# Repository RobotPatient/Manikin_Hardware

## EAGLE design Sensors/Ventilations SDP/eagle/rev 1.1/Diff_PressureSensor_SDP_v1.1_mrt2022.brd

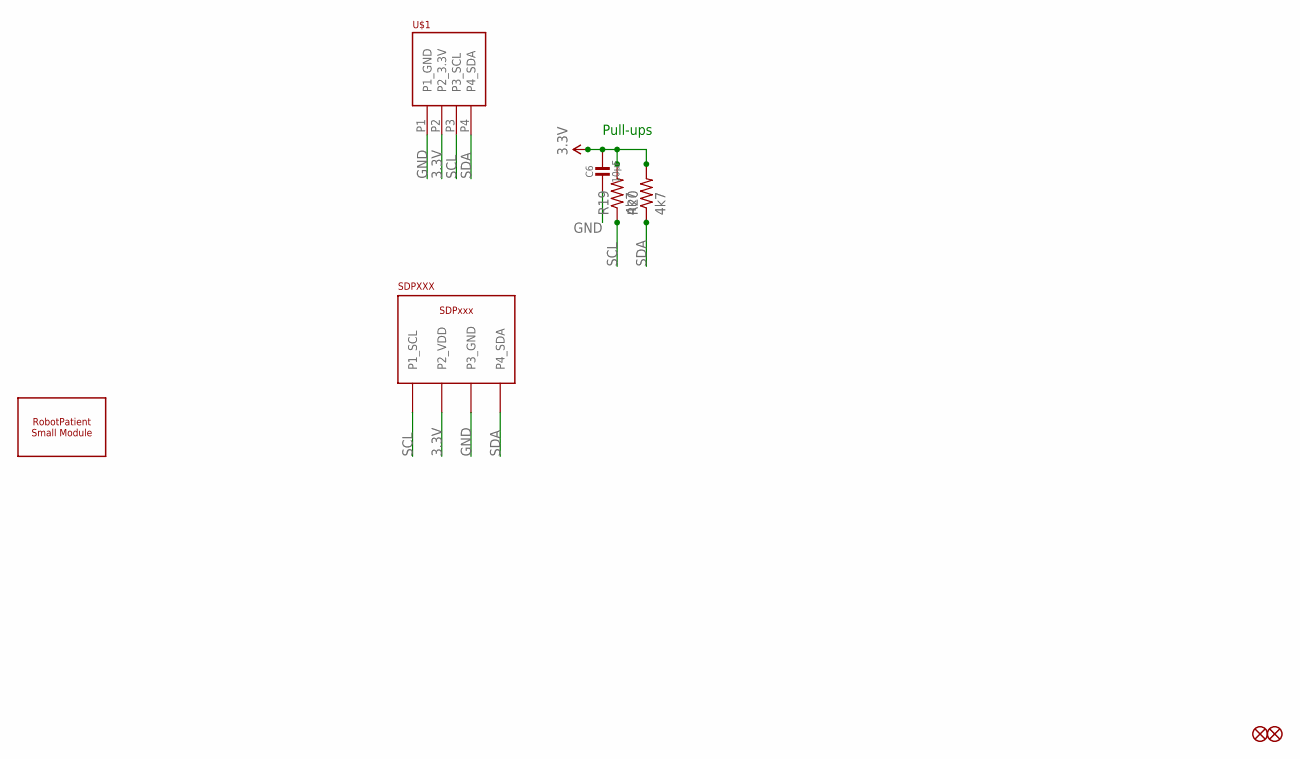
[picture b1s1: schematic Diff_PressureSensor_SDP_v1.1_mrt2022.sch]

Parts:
C6: 10µF; 0805-NO
FID1, FID2: FIDUCIAL""; FIDUCIAL_1MM
R19, R20: 4k7; 0603-RES
SDP810: SDPXXX
U$1: PHOENIX_PTSM_M4_THANGLE; PTSM_M4_TH
U$2: ROBOTPATIENT_SMALL_MODULEBOARD; RP_SMALL_SENSOR_OUTLINE

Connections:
3.3V: C6.1, R19.2, R20.2, SDP810.P3_VCC (P2_VDD), U$1.P2 (P2_3.3V)
GND: C6.2, SDP810.P2_GND (P3_GND), U$1.P1 (P1_GND)
SCL: R19.1, SDP810.P4_CLK (P1_SCL), U$1.P3 (P3_SCL)
SDA: R20.1, SDP810.P1_SDA (P4_SDA), U$1.P4 (P4_SDA)

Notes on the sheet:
Pull-ups

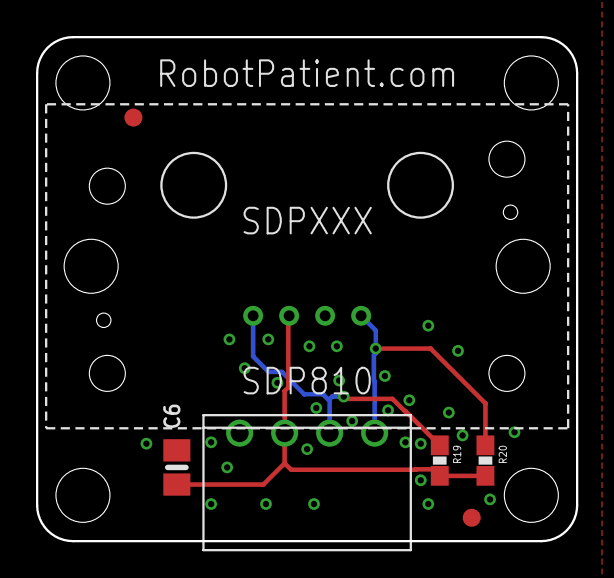
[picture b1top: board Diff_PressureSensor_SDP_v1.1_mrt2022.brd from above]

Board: 2 copper layers, 30.0 x 28.0 mm, 8 parts (0 on the bottom side), 4 nets.

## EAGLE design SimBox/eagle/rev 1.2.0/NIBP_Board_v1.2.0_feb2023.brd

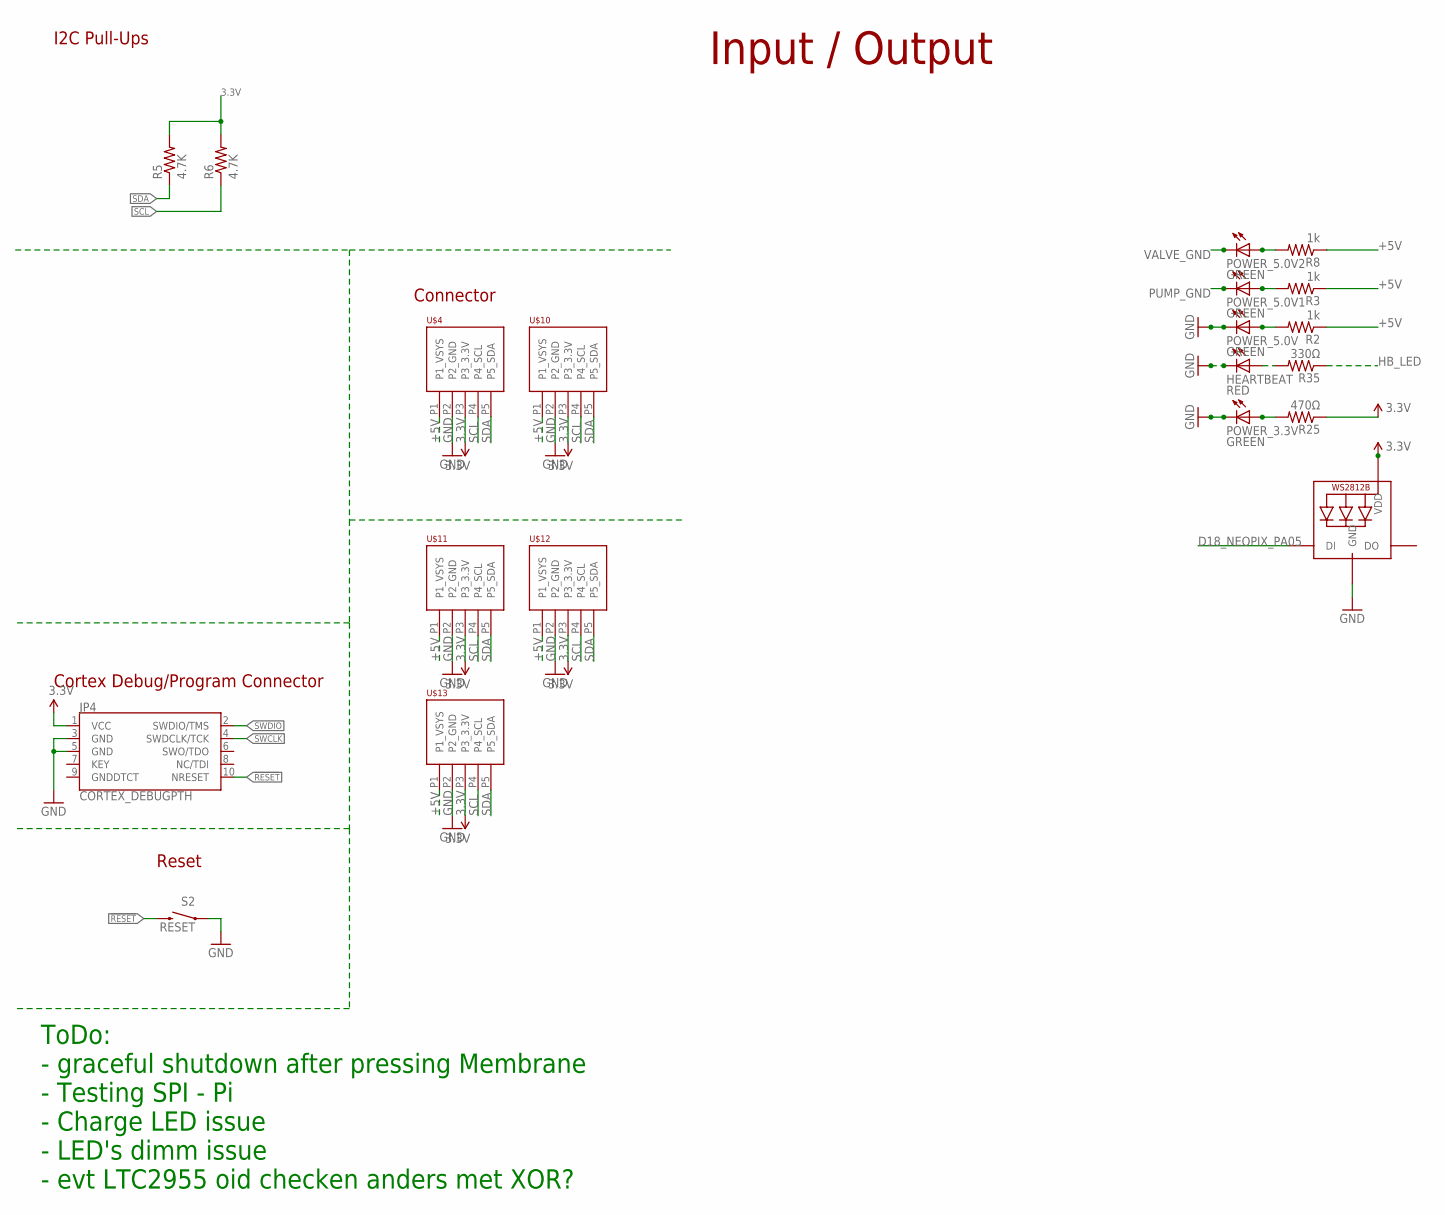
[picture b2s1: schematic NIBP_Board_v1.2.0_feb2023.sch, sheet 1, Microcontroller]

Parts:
HEARTBEAT: RED; LED-0603
JP4: CORTEX_DEBUGPTH; 2X5-PTH-1.27MM
LED1: WS2812B3535; LED3535
POWER_3.3V, POWER_5.0V, POWER_5.0V1, POWER_5.0V2: GREEN; LED-0603
R2, R3, R8: 1k; 0603-RES
R5, R6: 4.7K; 0603-RES@1
R25: 470Ω; 0603-RES
R35: 330Ω; 0603-RES
S2: RESET; TACTILE_SWITCH_SMD_4.6X2.8MM
U$4, U$10, U$11, U$12, U$13: PHOENIX_PTSM_M5_TH; PTSM_M5_THRHOLE

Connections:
3.3V: JP4.1 (VCC), LED1.2 (VDD), R5.2, R6.2, R25.1, U$4.P3 (P3_3.3V), U$10.P3 (P3_3.3V), U$11.P3 (P3_3.3V), U$12.P3 (P3_3.3V), U$13.P3 (P3_3.3V); also elsewhere on the board
!RESET: JP4.10 (NRESET), S2.3 (2), S2.4 (2); also elsewhere on the board
+5V: R2.1, R3.1, R8.1, U$4.P1 (P1_VSYS), U$10.P1 (P1_VSYS), U$11.P1 (P1_VSYS), U$12.P1 (P1_VSYS), U$13.P1 (P1_VSYS); also elsewhere on the board
D18_NEOPIX_PA05: LED1.1 (DI); also elsewhere on the board
GND: HEARTBEAT.C, JP4.3 (GND), JP4.5 (GND), LED1.4 (GND), POWER_3.3V.C, POWER_5.0V.C, S2.1, S2.2 (1), U$4.P2 (P2_GND), U$10.P2 (P2_GND), U$11.P2 (P2_GND), U$12.P2 (P2_GND), U$13.P2 (P2_GND); also elsewhere on the board
HB_LED: R35.1; also elsewhere on the board
unnamed: POWER_5.0V.A, R2.2
unnamed: POWER_5.0V1.A, R3.2
unnamed: POWER_5.0V2.A, R8.2
unnamed: POWER_3.3V.A, R25.2
unnamed: HEARTBEAT.A, R35.2
PUMP_GND: POWER_5.0V1.C; also elsewhere on the board
SCL: R6.1, U$4.P4 (P4_SCL), U$10.P4 (P4_SCL), U$11.P4 (P4_SCL), U$12.P4 (P4_SCL), U$13.P4 (P4_SCL); also elsewhere on the board
SDA: R5.1, U$4.P5 (P5_SDA), U$10.P5 (P5_SDA), U$11.P5 (P5_SDA), U$12.P5 (P5_SDA), U$13.P5 (P5_SDA); also elsewhere on the board
SWCLK: JP4.4 (SWDCLK/TCK); also elsewhere on the board
SWDIO: JP4.2 (SWDIO/TMS); also elsewhere on the board
VALVE_GND: POWER_5.0V2.C; also elsewhere on the board

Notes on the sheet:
Cortex Debug/Program Connector
I2C Pull-Ups
Input / Output
Connector
Reset
ToDo: - graceful shutdown after pressing Membrane - Testing SPI - Pi - Charge LED issue - LED's dimm issue - evt LTC2955 oid checken anders met XOR?

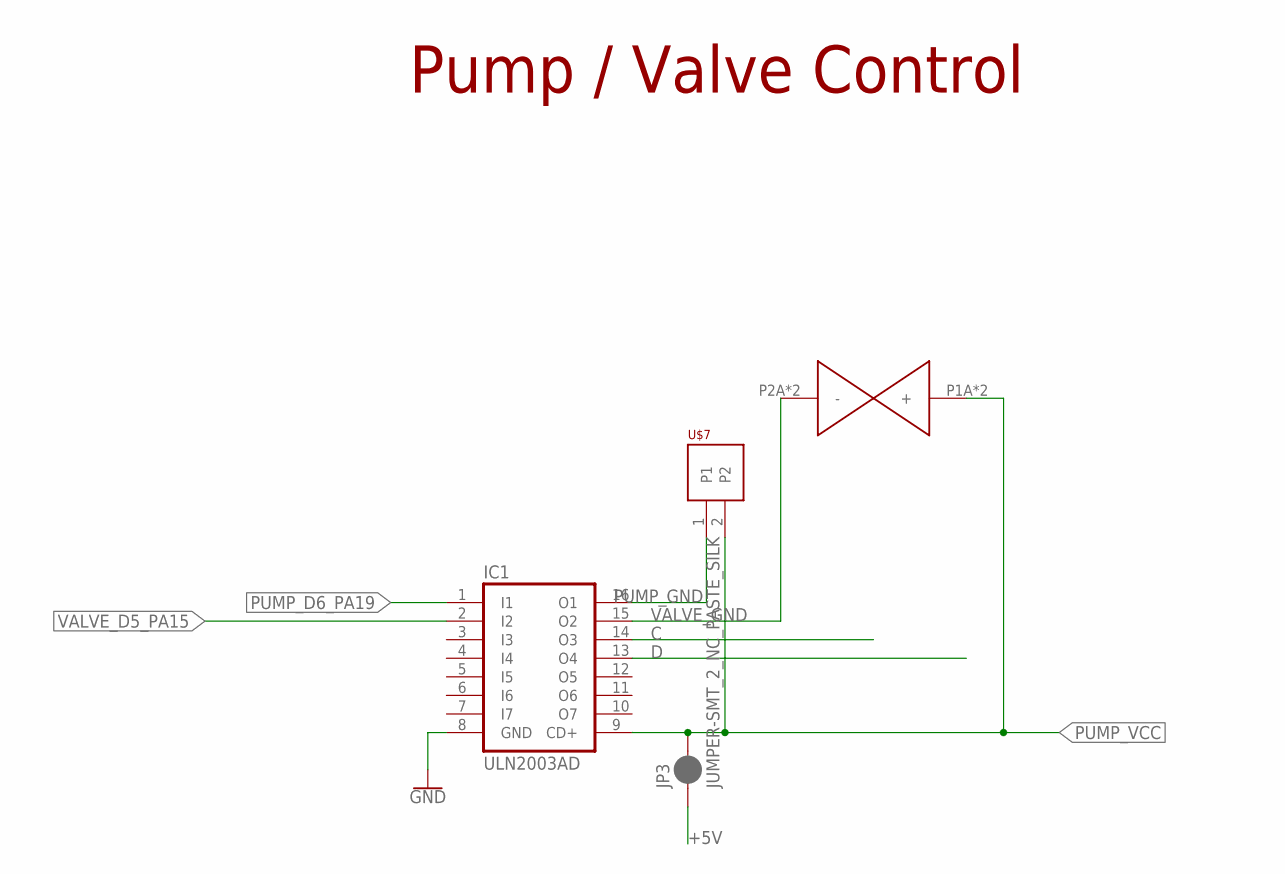
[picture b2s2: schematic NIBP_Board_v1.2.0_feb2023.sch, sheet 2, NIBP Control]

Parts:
IC1: ULN2003AD; SO16
JP3: JUMPER-SMT_2_NC_PASTE_SILK; SMT-JUMPER_2_NC_PASTE_SILK
U$6: VALVE_NIBP
U$7: PHOENIX_PTSM_M2TH; PTSM_M2_THRHOLE

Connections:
+5V: JP3.1; also elsewhere on the board
C: IC1.14 (O3)
D: IC1.13 (O4)
GND: IC1.8 (GND); also elsewhere on the board
PUMP_D6_PA19: IC1.1 (I1); also elsewhere on the board
PUMP_GND: IC1.16 (O1), U$7.1; also elsewhere on the board
PUMP_VCC: IC1.9 (CD+), JP3.2, U$6.P1A (+), U$6.P1B (+), U$7.2
VALVE_D5_PA15: IC1.2 (I2); also elsewhere on the board
VALVE_GND: IC1.15 (O2), U$6.P2A (-), U$6.P2B (-); also elsewhere on the board

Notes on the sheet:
Pump / Valve Control

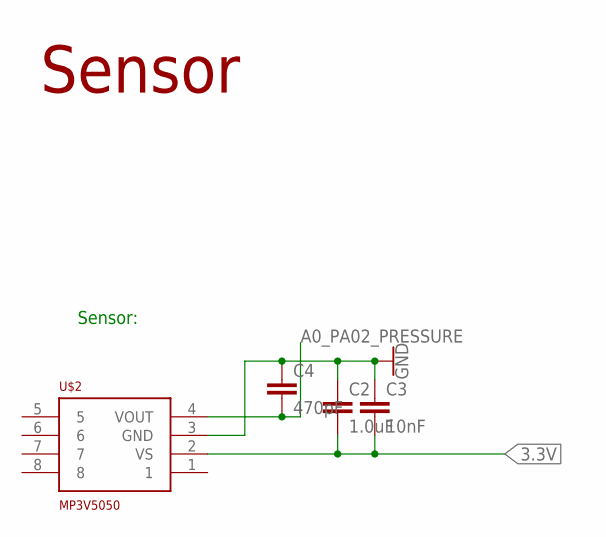
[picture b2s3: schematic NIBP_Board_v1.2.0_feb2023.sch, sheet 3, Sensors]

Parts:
C2: 1.0uF; 0603
C3: 10nF; 0603
C4: 470pF; 0603
U$2: MP3V5050; PRESSURE_SENSOR

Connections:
3.3V: C2.2, C3.2, U$2.2 (VS); also elsewhere on the board
A0_PA02_PRESSURE: C4.2, U$2.4 (VOUT); also elsewhere on the board
GND: C2.1, C3.1, C4.1, U$2.3 (GND); also elsewhere on the board

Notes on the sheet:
Sensor:
Sensor

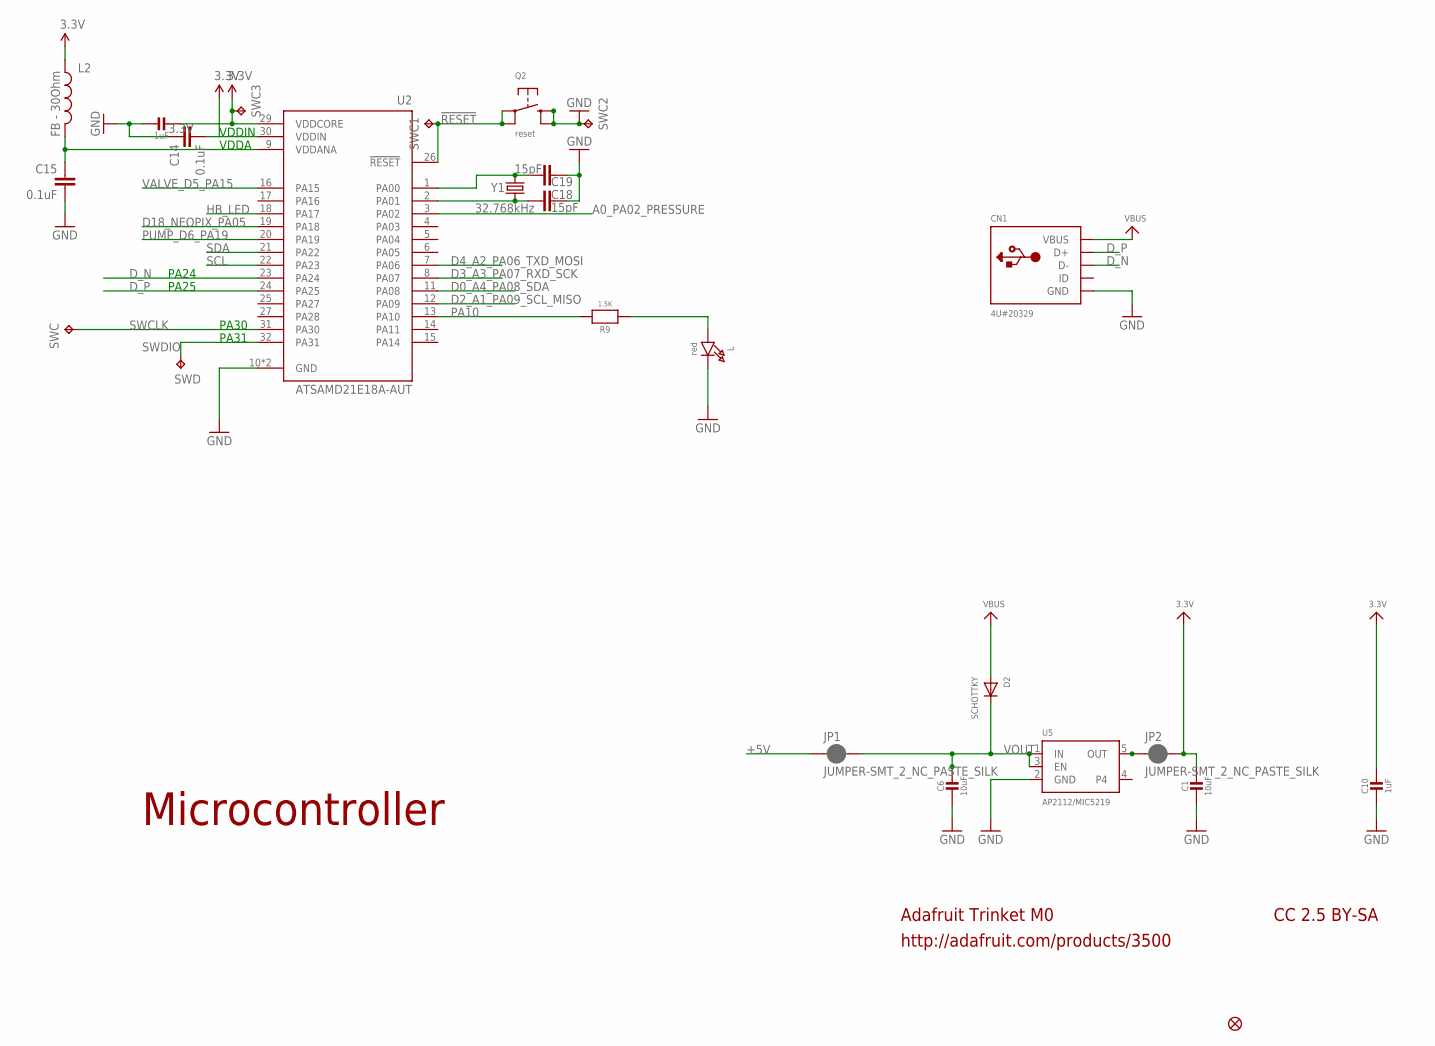
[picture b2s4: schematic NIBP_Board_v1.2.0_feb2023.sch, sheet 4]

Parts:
C1, C6: 10uF; 0805-NO
C10, C13: 1uF; 0603-NO
C14, C15: 0.1uF; 0402-CAP
C18, C19: 15pF; 0402-CAP
CN1: 4U#20329; 4UCONN_20329_V2
D2: SCHOTTKY; SOD-123FL
JP1, JP2: JUMPER-SMT_2_NC_PASTE_SILK; SMT-JUMPER_2_NC_PASTE_SILK
L: red; CHIPLED_0603_NOOUTLINE
L2: FB - 30Ohm; 0603
Q2: reset; BTN_KMR2_4.6X2.8
R9: 1.5K; 0603-NO
SWC, SWC1, SWC2, SWC3: TPB1,27; B1,27
SWD: TPB1,27; B1,27
U2: ATSAMD21E18A-AUT; QFP80P900X900X120-32N
U5: AP2112/MIC5219; SOT23-5
U$15: FIDUCIAL_1MM
Y1: 32.768kHz; CRYSTAL-SMD-3.2X1.5MM

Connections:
3.3V: C1.1, C10.1, C13.1, JP2.2, L2.1, SWC3.TP, U2.29 (VDDCORE); also elsewhere on the board
!RESET: Q2.A, Q2.A' (P1), SWC1.TP, U2.26 (!RESET); also elsewhere on the board
+5V: JP1.1; also elsewhere on the board
A0_PA02_PRESSURE: U2.3 (PA02); also elsewhere on the board
D0_A4_PA08_SDA: U2.11 (PA08)
D2_A1_PA09_SCL_MISO: U2.12 (PA09)
D3_A3_PA07_RXD_SCK: U2.8 (PA07)
D4_A2_PA06_TXD_MOSI: U2.7 (PA06)
D18_NEOPIX_PA05: U2.19 (PA18); also elsewhere on the board
D_N: CN1.D-, U2.23 (PA24)
D_P: CN1.D+, U2.24 (PA25)
GND: C1.2, C6.2, C10.2, C13.2, C14.1, C15.2, C18.1, C19.2, CN1.BASE@1 (GND), CN1.BASE@2 (GND), CN1.GND, CN1.SPRT@1 (GND), CN1.SPRT@2 (GND), CN1.SPRT@3 (GND), CN1.SPRT@4 (GND), L.C, Q2.B (S), Q2.B' (S1), SWC2.TP, U2.10 (GND), U2.28 (GND), U5.2 (GND); also elsewhere on the board
HB_LED: U2.18 (PA17); also elsewhere on the board
unnamed: L.A, R9.1
unnamed: C14.2, U2.30 (VDDIN)
unnamed: C18.2, U2.2 (PA01), Y1.P$2 (2)
unnamed: C19.1, U2.1 (PA00), Y1.P$1 (1)
OUT: JP2.1, U5.5 (OUT)
PA10: R9.2, U2.13 (PA10)
PUMP_D6_PA19: U2.20 (PA19); also elsewhere on the board
SCL: U2.22 (PA23); also elsewhere on the board
SDA: U2.21 (PA22); also elsewhere on the board
SWCLK: SWC.TP, U2.31 (PA30); also elsewhere on the board
SWDIO: SWD.TP, U2.32 (PA31); also elsewhere on the board
VALVE_D5_PA15: U2.16 (PA15); also elsewhere on the board
VBUS: CN1.VBUS, D2.A
VDDANA1: C15.1, L2.2, U2.9 (VDDANA)
VOUT: C6.1, D2.C, JP1.2, U5.1 (IN), U5.3 (EN)

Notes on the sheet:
Adafruit Trinket M0
http://adafruit.com/products/3500
CC 2.5 BY-SA
PA24
PA25
PA30
PA31
VDDA
VDDIN
Microcontroller

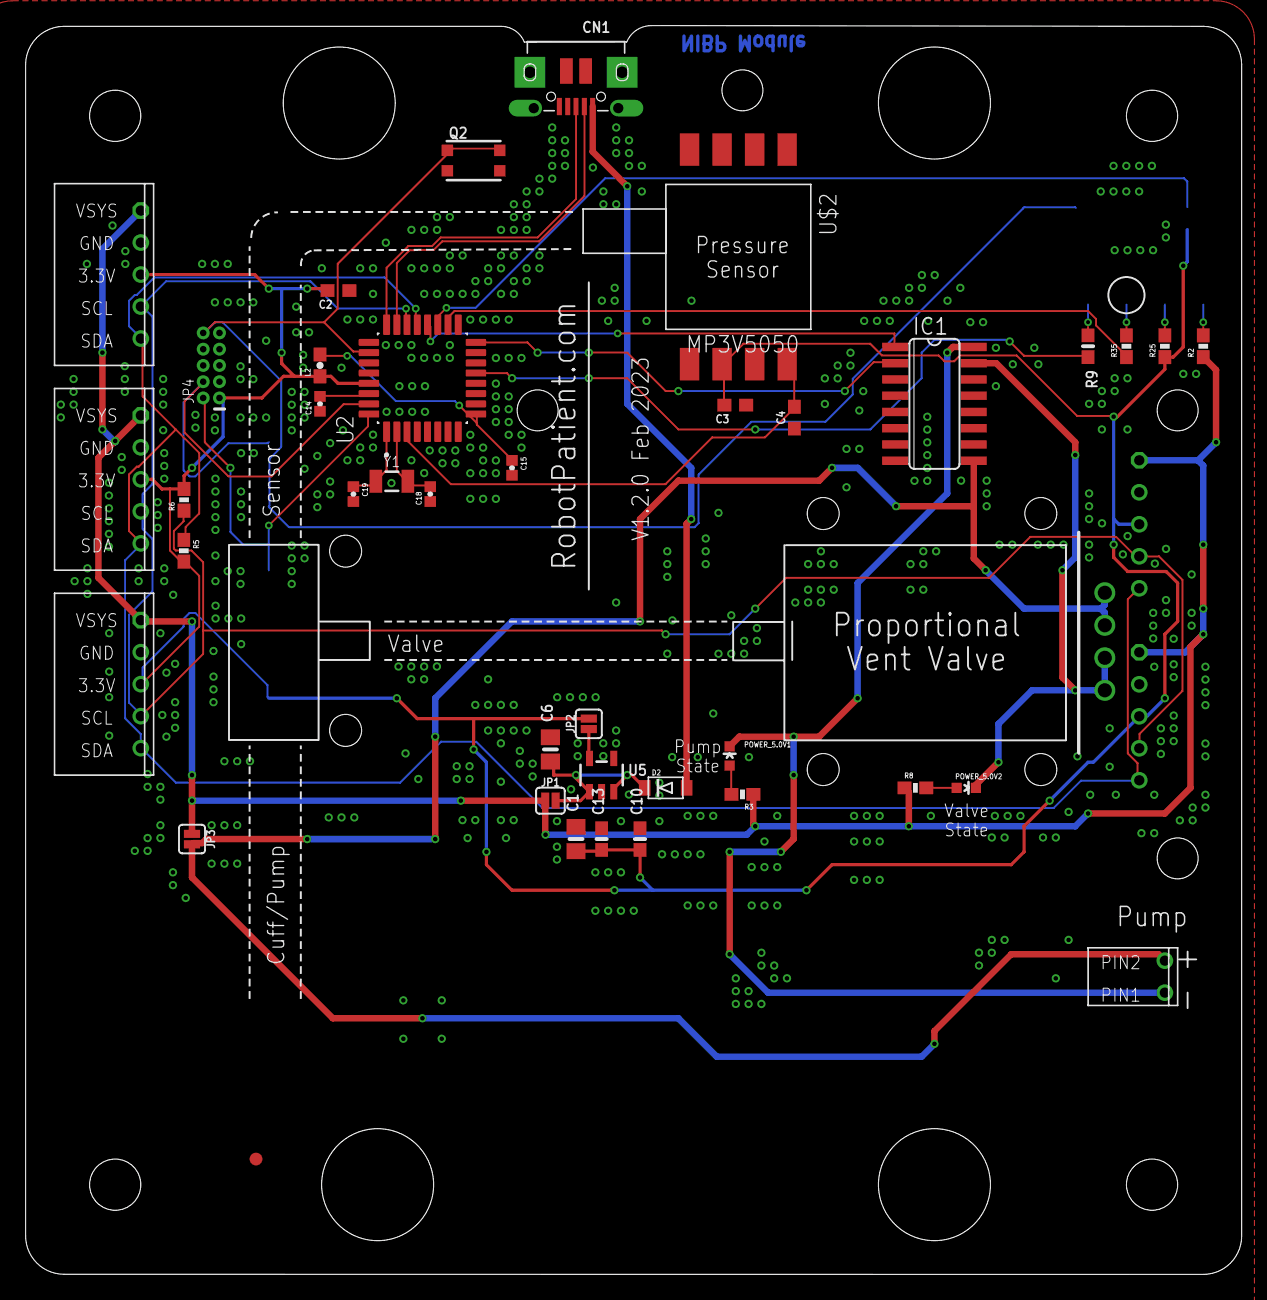
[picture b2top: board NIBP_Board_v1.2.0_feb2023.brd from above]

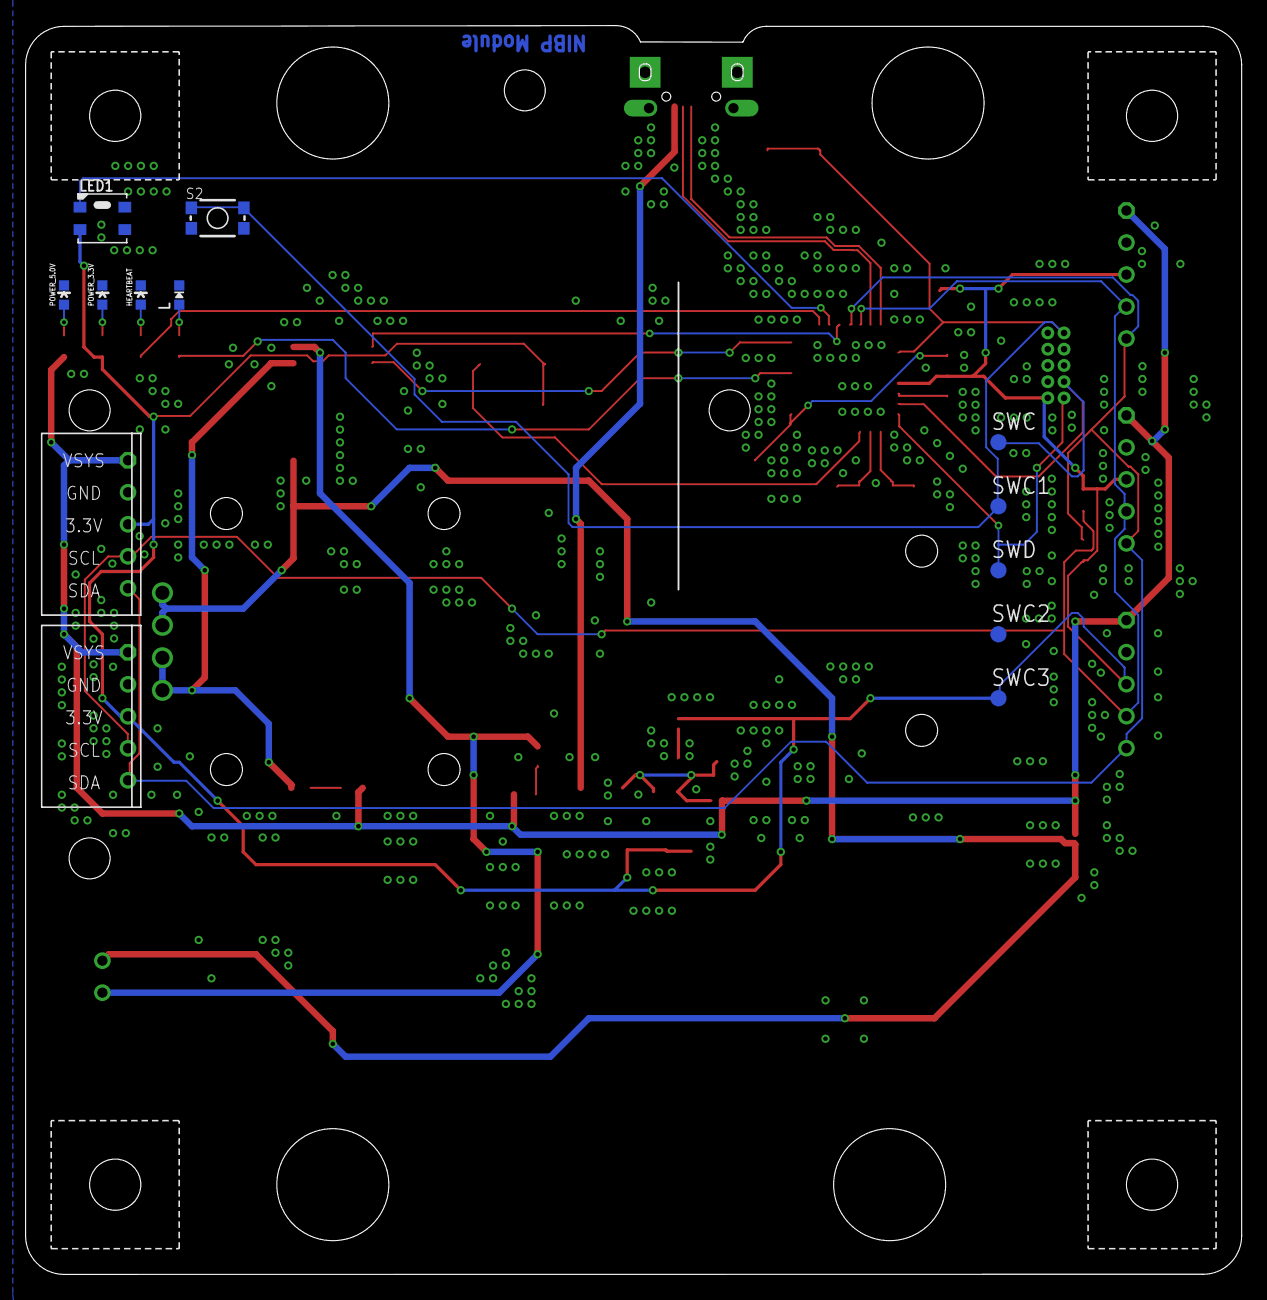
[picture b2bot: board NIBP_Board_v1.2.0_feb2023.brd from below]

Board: 2 copper layers, 95.0 x 97.6 mm, 57 parts (13 on the bottom side), 32 nets.

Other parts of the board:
U$3, U$5, U$9, U$40: WA-SNAD

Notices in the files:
parts and their libraries:
microbuilder: This work is placed in the public domain, and may be freely used for commercial and non-commercial work with the following conditions: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
SparkFun-Resistors: Licensing: Creative Commons ShareAlike 4.0 International - https://creativecommons.org/licenses/by-sa/4.0
